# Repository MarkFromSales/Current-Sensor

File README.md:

# Current-Sensor
Multiple high side current sensor array intended to mate up with Nixie tube project

Inspired by, and foundation of the design and code from, Adafruit's INA219 breakout - https://www.adafruit.com/product/904

Currently working on the code using the breadboard prototype before sending out for fabrication.

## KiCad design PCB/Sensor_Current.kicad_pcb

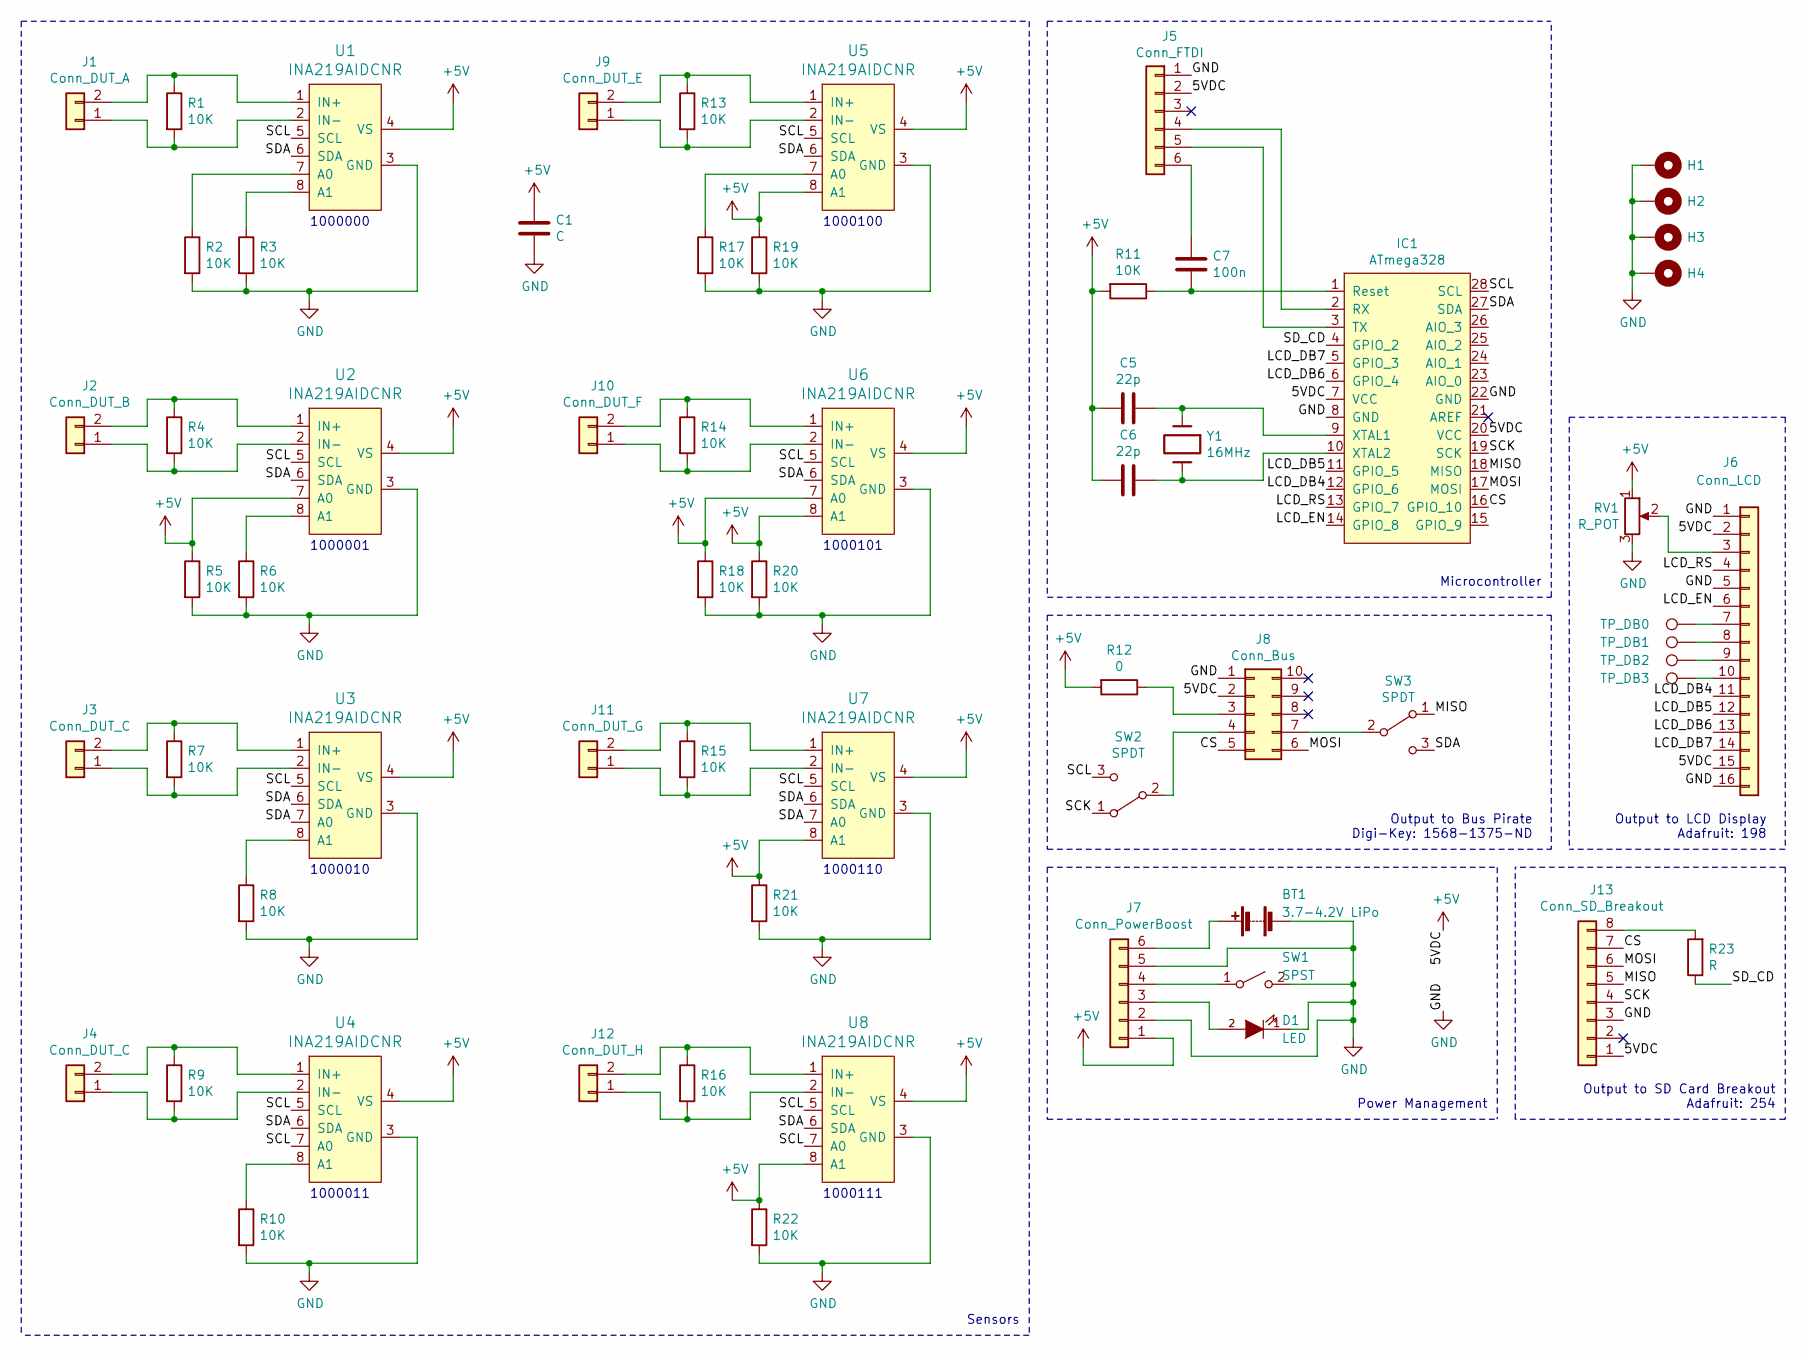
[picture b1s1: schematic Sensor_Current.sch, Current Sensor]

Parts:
BT1: 3.7-4.2V LiPo; BatteryHolder_Keystone_3034_1x20mm
C1: C; C_1206_3216Metric_Pad1.42x1.75mm_HandSolder
C5, C6: 22p; C_1206_3216Metric_Pad1.42x1.75mm_HandSolder
C7: 100n; C_1206_3216Metric_Pad1.42x1.75mm_HandSolder
D1: LED; LED_1206_3216Metric_Pad1.42x1.75mm_HandSolder
H1, H2, H3, H4: MountingHole_Pad; MountingHole_3.2mm_M3_Pad
IC1: ATmega328; DIP-28_W7.62mm_Socket
J1: Conn_DUT_A; PinHeader_1x02_P2.54mm_Vertical
J2: Conn_DUT_B; PinHeader_1x02_P2.54mm_Vertical
J3, J4: Conn_DUT_C; PinHeader_1x02_P2.54mm_Vertical
J5: Conn_FTDI; PinHeader_1x06_P2.54mm_Vertical
J6: Conn_LCD; PinHeader_1x16_P2.54mm_Vertical
J7: Conn_PowerBoost; PinSocket_1x06_P2.54mm_Vertical
J8: Conn_Bus; PinSocket_2x05_P2.54mm_Vertical
J9: Conn_DUT_E; PinHeader_1x02_P2.54mm_Vertical
J10: Conn_DUT_F; PinHeader_1x02_P2.54mm_Vertical
J11: Conn_DUT_G; PinHeader_1x02_P2.54mm_Vertical
J12: Conn_DUT_H; PinHeader_1x02_P2.54mm_Vertical
J13: Conn_SD_Breakout; PinHeader_1x08_P2.54mm_Vertical
R1, R2, R3, R4, R5, R6, R7, R8, R9, R10, R11, R13, R14, R15, R16, R17, R18, R19, R20, R21, R22: 10K; R_0805_2012Metric_Pad1.15x1.40mm_HandSolder
R12: 0; R_0805_2012Metric_Pad1.15x1.40mm_HandSolder
R23: R; R_0805_2012Metric_Pad1.15x1.40mm_HandSolder
RV1: R_POT; Potentiometer_Bourns_3386F_Vertical
SW1: SPST; PinHeader_1x02_P2.54mm_Vertical
SW2, SW3: SPDT; SW_SPDT_PCM12
TP_DB0, TP_DB1, TP_DB2, TP_DB3: TestPoint; TestPoint_Pad_D1.0mm
U1, U2, U3, U4, U5, U6, U7, U8: INA219AIDCNR; SOT-23-8; MPN INA219AIDCNR; Digi-Key_PN 296-23770-1-ND
Y1: 16MHz; Crystal_HC49-U_Vertical

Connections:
+5V: C1.1, C5.2, C6.2, IC1.7 (VCC), IC1.20 (VCC), J5.2, J6.2, J6.15, J7.1, J8.2, J13.1, R5.1, R11.2, R12.2, R18.1, R19.1, R20.1, R21.1, R22.1, RV1.1, U1.4 (VS), U2.4 (VS), U2.7 (A0), U3.4 (VS), U4.4 (VS), U5.4 (VS), U5.8 (A1), U6.4 (VS), U6.7 (A0), U6.8 (A1), U7.4 (VS), U7.8 (A1), U8.4 (VS), U8.8 (A1)
/CS: IC1.16 (GPIO_10), J8.5, J13.7
/LCD_DB4: IC1.12 (GPIO_6), J6.11
/LCD_DB5: IC1.11 (GPIO_5), J6.12
/LCD_DB6: IC1.6 (GPIO_4), J6.13
/LCD_DB7: IC1.5 (GPIO_3), J6.14
/LCD_EN: IC1.14 (GPIO_8), J6.6
/LCD_RS: IC1.13 (GPIO_7), J6.4
/MISO: IC1.18 (MISO), J13.5, SW3.1 (A)
/MOSI: IC1.17 (MOSI), J8.6, J13.6
/SCK: IC1.19 (SCK), J13.4, SW2.1 (A)
/SCL: IC1.28 (SCL), SW2.3 (C), U1.5 (SCL), U2.5 (SCL), U3.5 (SCL), U4.5 (SCL), U4.7 (A0), U5.5 (SCL), U6.5 (SCL), U7.5 (SCL), U8.5 (SCL), U8.7 (A0)
/SDA: IC1.27 (SDA), SW3.3 (C), U1.6 (SDA), U2.6 (SDA), U3.6 (SDA), U3.7 (A0), U4.6 (SDA), U5.6 (SDA), U6.6 (SDA), U7.6 (SDA), U7.7 (A0), U8.6 (SDA)
/SD_CD: IC1.4 (GPIO_2), R23.1
GND: BT1.2 (-), C1.2, D1.1 (K), H1.1, H2.1, H3.1, H4.1, IC1.8 (GND), IC1.22 (GND), J5.1, J6.1, J6.5, J6.16, J7.2, J7.5, J8.1, J13.3, R2.2, R3.2, R5.2, R6.2, R8.2, R10.2, R17.2, R18.2, R19.2, R20.2, R21.2, R22.2, RV1.3, SW1.2 (B), U1.3 (GND), U2.3 (GND), U3.3 (GND), U4.3 (GND), U5.3 (GND), U6.3 (GND), U7.3 (GND), U8.3 (GND)
unnamed: BT1.1 (+), J7.6
unnamed: C5.1, IC1.9 (XTAL1), Y1.1
unnamed: C6.1, IC1.10 (XTAL2), Y1.2
unnamed: C7.1, J5.6
unnamed: C7.2, IC1.1 (Reset), R11.1
unnamed: D1.2 (A), J7.3
unnamed: IC1.2 (RX), J5.4
unnamed: IC1.3 (TX), J5.5
unnamed: J1.1, R1.2, U1.2 (IN-)
unnamed: J1.2, R1.1, U1.1 (IN+)
unnamed: J2.1, R4.2, U2.2 (IN-)
unnamed: J2.2, R4.1, U2.1 (IN+)
unnamed: J3.1, R7.2, U3.2 (IN-)
unnamed: J3.2, R7.1, U3.1 (IN+)
unnamed: J4.1, R9.2, U4.2 (IN-)
unnamed: J4.2, R9.1, U4.1 (IN+)
unnamed: J6.3, RV1.2
unnamed: J6.7, TP_DB0.1
unnamed: J6.8, TP_DB1.1
unnamed: J6.9, TP_DB2.1
unnamed: J6.10, TP_DB3.1
unnamed: J7.4, SW1.1 (A)
unnamed: J8.3, R12.1
unnamed: J8.4, SW2.2 (B)
unnamed: J8.7, SW3.2 (B)
unnamed: J9.1, R13.2, U5.2 (IN-)
unnamed: J9.2, R13.1, U5.1 (IN+)
unnamed: J10.1, R14.2, U6.2 (IN-)
unnamed: J10.2, R14.1, U6.1 (IN+)
unnamed: J11.1, R15.2, U7.2 (IN-)
unnamed: J11.2, R15.1, U7.1 (IN+)
unnamed: J12.1, R16.2, U8.2 (IN-)
unnamed: J12.2, R16.1, U8.1 (IN+)
unnamed: J13.8, R23.2
unnamed: R2.1, U1.7 (A0)
unnamed: R3.1, U1.8 (A1)
unnamed: R6.1, U2.8 (A1)
unnamed: R8.1, U3.8 (A1)
unnamed: R10.1, U4.8 (A1)
unnamed: R17.1, U5.7 (A0)

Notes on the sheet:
1000000
1000001
1000010
1000011
Sensors
Power Management
Output to Bus Pirate Digi-Key: 1568-1375-ND
Output to SD Card Breakout Adafruit: 254
1000100
1000101
1000110
1000111
Output to LCD Display Adafruit: 198
Microcontroller

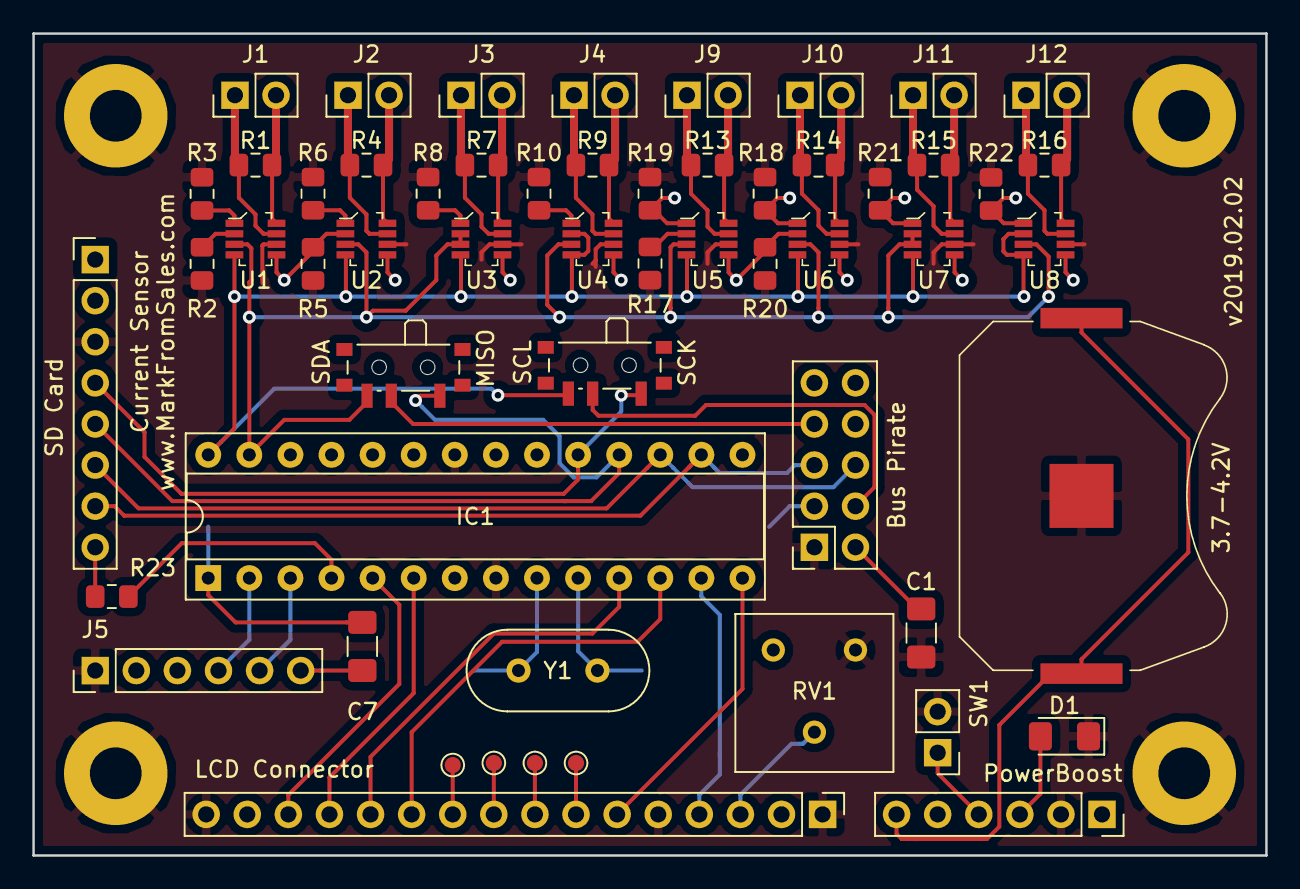
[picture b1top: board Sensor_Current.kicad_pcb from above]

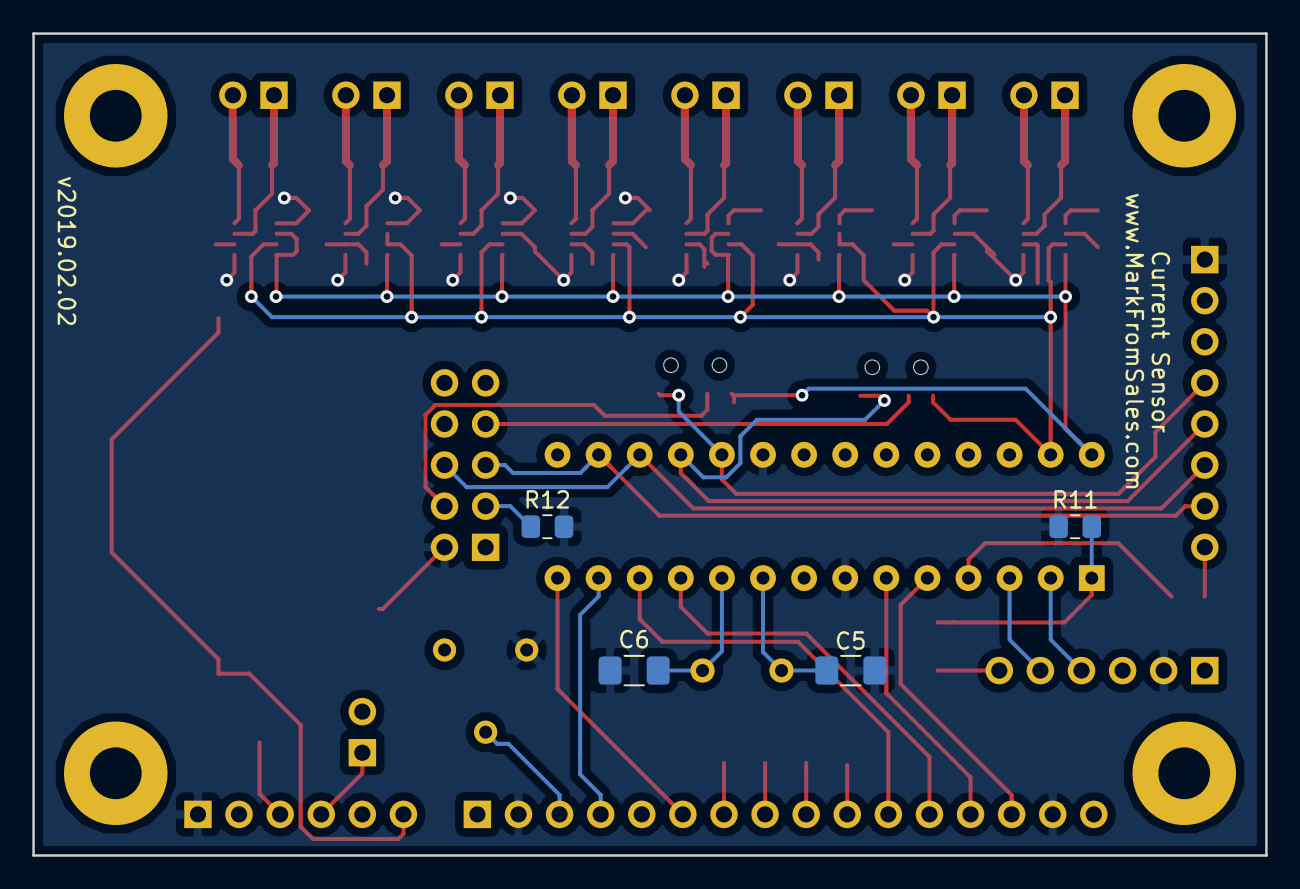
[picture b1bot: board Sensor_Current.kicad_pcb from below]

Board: 2 copper layers, 76.2 x 50.8 mm, 64 parts (4 on the bottom side), 55 nets.

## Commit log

2019-02-02 Initial upload
2019-02-03 Updated PCB layout
2019-02-03 File rename
2019-02-13 Updated structure
